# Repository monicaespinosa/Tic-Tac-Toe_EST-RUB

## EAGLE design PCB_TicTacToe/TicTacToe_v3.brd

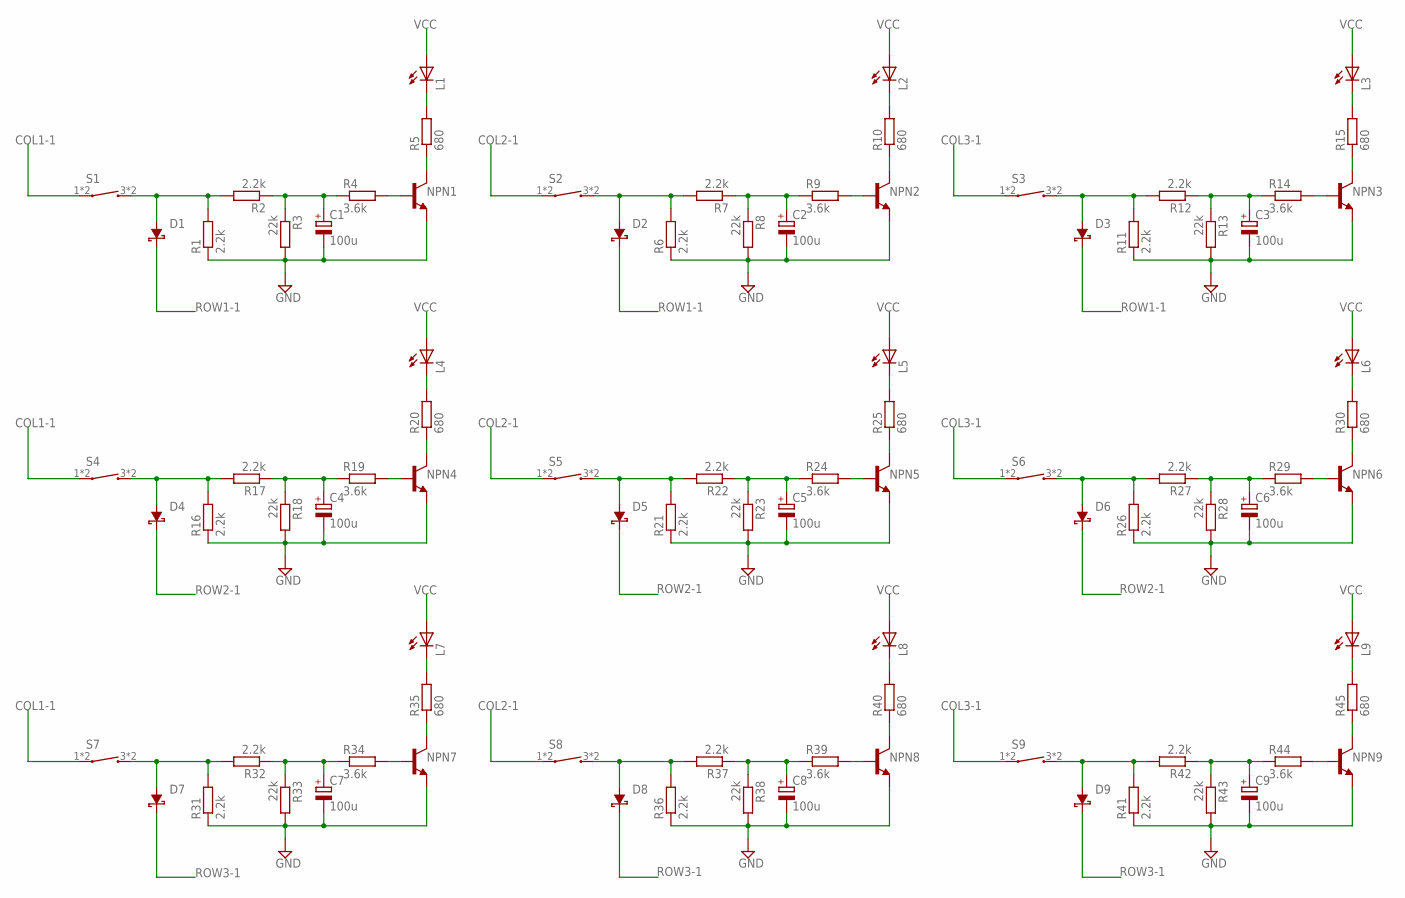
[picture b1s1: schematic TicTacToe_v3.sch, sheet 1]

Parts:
C1, C2, C3, C4, C5, C6, C7, C8, C9: 100u; T490A-COND
D1, D2, D3, D4, D5, D6, D7, D8, D9: PMEG3010EH; PMEG3010EH-SCHOTTKYDIODE
L1, L2, L3, L4, L5, L6, L7, L8, L9: 150060BS75003; WL-SMCW-LED(BLUE)
NPN1, NPN2, NPN3, NPN4, NPN5, NPN6, NPN7, NPN8, NPN9: BC848; BC848-NPN
R1, R2, R6, R7, R11, R12, R16, R17, R21, R22, R26, R27, R31, R32, R36, R37, R41, R42: 2.2k; R0603
R3, R8, R13, R18, R23, R28, R33, R38, R43: 22k; R0603
R4, R9, R14, R19, R24, R29, R34, R39, R44: 3.6k; R0603
R5, R10, R15, R20, R25, R30, R35, R40, R45: 680; R0603
S1, S2, S3, S4, S5, S6, S7, S8, S9: PTS647; PTS647-TACTSWITCH

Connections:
COL1-1: S1.1, S1.2 (1), S4.1, S4.2 (1), S7.1, S7.2 (1); also elsewhere on the board
COL2-1: S2.1, S2.2 (1), S5.1, S5.2 (1), S8.1, S8.2 (1); also elsewhere on the board
COL3-1: S3.1, S3.2 (1), S6.1, S6.2 (1), S9.1, S9.2 (1); also elsewhere on the board
GND: C1.2 (-), C2.2 (-), C3.2 (-), C4.2 (-), C5.2 (-), C6.2 (-), C7.2 (-), C8.2 (-), C9.2 (-), NPN1.2 (E), NPN2.2 (E), NPN3.2 (E), NPN4.2 (E), NPN5.2 (E), NPN6.2 (E), NPN7.2 (E), NPN8.2 (E), NPN9.2 (E), R1.1, R3.2, R6.1, R8.2, R11.1, R13.2, R16.1, R18.2, R21.1, R23.2, R26.1, R28.2, R31.1, R33.2, R36.1, R38.2, R41.1, R43.2; also elsewhere on the board
unnamed: D1.2 (A), R1.2, R2.2, S1.3 (2), S1.4 (2)
unnamed: C1.1 (+), R2.1, R3.1, R4.1
unnamed: NPN1.1 (B), R4.2
unnamed: D2.2 (A), R6.2, R7.2, S2.3 (2), S2.4 (2)
unnamed: C2.1 (+), R7.1, R8.1, R9.1
unnamed: NPN1.3 (C), R5.1
unnamed: L1.1 (C), R5.2
unnamed: NPN2.1 (B), R9.2
unnamed: D4.2 (A), R16.2, R17.2, S4.3 (2), S4.4 (2)
unnamed: NPN2.3 (C), R10.1
unnamed: L2.1 (C), R10.2
unnamed: C4.1 (+), R17.1, R18.1, R19.1
unnamed: D3.2 (A), R11.2, R12.2, S3.3 (2), S3.4 (2)
unnamed: C3.1 (+), R12.1, R13.1, R14.1
unnamed: NPN3.1 (B), R14.2
unnamed: NPN3.3 (C), R15.1
unnamed: L3.1 (C), R15.2
unnamed: NPN4.1 (B), R19.2
unnamed: NPN4.3 (C), R20.1
unnamed: L4.1 (C), R20.2
unnamed: D5.2 (A), R21.2, R22.2, S5.3 (2), S5.4 (2)
unnamed: C5.1 (+), R22.1, R23.1, R24.1
unnamed: NPN5.1 (B), R24.2
unnamed: NPN5.3 (C), R25.1
unnamed: L5.1 (C), R25.2
unnamed: D6.2 (A), R26.2, R27.2, S6.3 (2), S6.4 (2)
unnamed: C6.1 (+), R27.1, R28.1, R29.1
unnamed: NPN6.1 (B), R29.2
unnamed: NPN6.3 (C), R30.1
unnamed: L6.1 (C), R30.2
unnamed: D7.2 (A), R31.2, R32.2, S7.3 (2), S7.4 (2)
unnamed: C7.1 (+), R32.1, R33.1, R34.1
unnamed: NPN7.1 (B), R34.2
unnamed: NPN7.3 (C), R35.1
unnamed: L7.1 (C), R35.2
unnamed: D8.2 (A), R36.2, R37.2, S8.3 (2), S8.4 (2)
unnamed: C8.1 (+), R37.1, R38.1, R39.1
unnamed: NPN8.1 (B), R39.2
unnamed: NPN8.3 (C), R40.1
unnamed: L8.1 (C), R40.2
unnamed: D9.2 (A), R41.2, R42.2, S9.3 (2), S9.4 (2)
unnamed: C9.1 (+), R42.1, R43.1, R44.1
unnamed: NPN9.1 (B), R44.2
unnamed: NPN9.3 (C), R45.1
unnamed: L9.1 (C), R45.2
ROW1-1: D1.1 (C), D2.1 (C), D3.1 (C); also elsewhere on the board
ROW2-1: D4.1 (C), D5.1 (C), D6.1 (C); also elsewhere on the board
ROW3-1: D7.1 (C), D8.1 (C), D9.1 (C); also elsewhere on the board
VCC: L1.2 (A), L2.2 (A), L3.2 (A), L4.2 (A), L5.2 (A), L6.2 (A), L7.2 (A), L8.2 (A), L9.2 (A); also elsewhere on the board

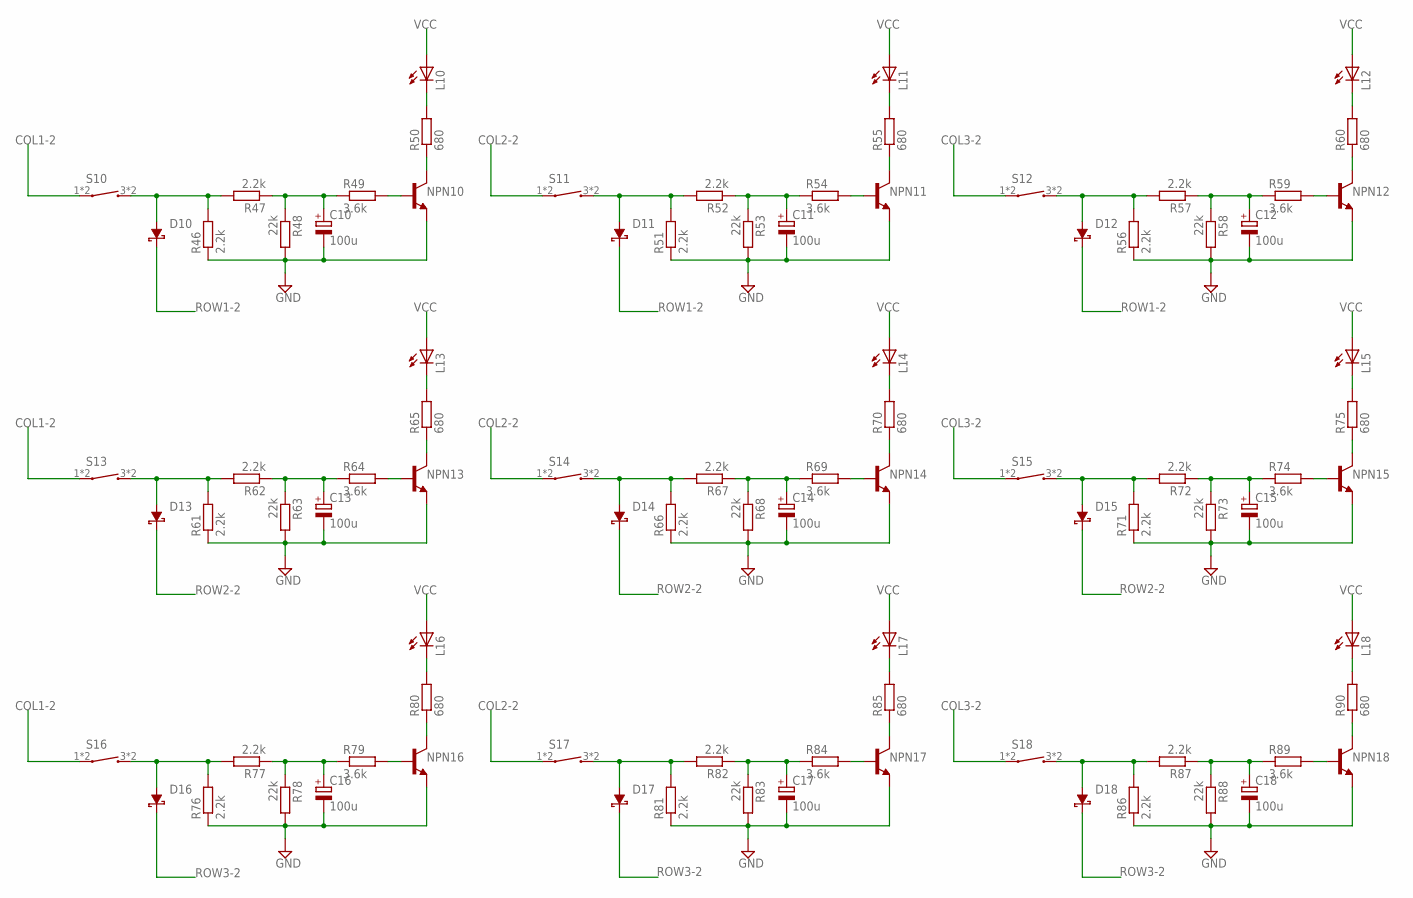
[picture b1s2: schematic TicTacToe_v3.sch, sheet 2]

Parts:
C10, C11, C12, C13, C14, C15, C16, C17, C18: 100u; T490A-COND
D10, D11, D12, D13, D14, D15, D16, D17, D18: PMEG3010EH; PMEG3010EH-SCHOTTKYDIODE
L10, L11, L12, L13, L14, L15, L16, L17, L18: 150060BS75003; WL-SMCW-LED(BLUE)
NPN10, NPN11, NPN12, NPN13, NPN14, NPN15, NPN16, NPN17, NPN18: BC848; BC848-NPN
R46, R47, R51, R52, R56, R57, R61, R62, R66, R67, R71, R72, R76, R77, R81, R82, R86, R87: 2.2k; R0603
R48, R53, R58, R63, R68, R73, R78, R83, R88: 22k; R0603
R49, R54, R59, R64, R69, R74, R79, R84, R89: 3.6k; R0603
R50, R55, R60, R65, R70, R75, R80, R85, R90: 680; R0603
S10, S11, S12, S13, S14, S15, S16, S17, S18: PTS647; PTS647-TACTSWITCH

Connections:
COL1-2: S10.1, S10.2 (1), S13.1, S13.2 (1), S16.1, S16.2 (1); also elsewhere on the board
COL2-2: S11.1, S11.2 (1), S14.1, S14.2 (1), S17.1, S17.2 (1); also elsewhere on the board
COL3-2: S12.1, S12.2 (1), S15.1, S15.2 (1), S18.1, S18.2 (1); also elsewhere on the board
GND: C10.2 (-), C11.2 (-), C12.2 (-), C13.2 (-), C14.2 (-), C15.2 (-), C16.2 (-), C17.2 (-), C18.2 (-), NPN10.2 (E), NPN11.2 (E), NPN12.2 (E), NPN13.2 (E), NPN14.2 (E), NPN15.2 (E), NPN16.2 (E), NPN17.2 (E), NPN18.2 (E), R46.1, R48.2, R51.1, R53.2, R56.1, R58.2, R61.1, R63.2, R66.1, R68.2, R71.1, R73.2, R76.1, R78.2, R81.1, R83.2, R86.1, R88.2; also elsewhere on the board
unnamed: D10.2 (A), R46.2, R47.2, S10.3 (2), S10.4 (2)
unnamed: C10.1 (+), R47.1, R48.1, R49.1
unnamed: NPN10.1 (B), R49.2
unnamed: NPN10.3 (C), R50.1
unnamed: L10.1 (C), R50.2
unnamed: D11.2 (A), R51.2, R52.2, S11.3 (2), S11.4 (2)
unnamed: C11.1 (+), R52.1, R53.1, R54.1
unnamed: NPN11.1 (B), R54.2
unnamed: NPN11.3 (C), R55.1
unnamed: L11.1 (C), R55.2
unnamed: D12.2 (A), R56.2, R57.2, S12.3 (2), S12.4 (2)
unnamed: C12.1 (+), R57.1, R58.1, R59.1
unnamed: NPN12.1 (B), R59.2
unnamed: NPN12.3 (C), R60.1
unnamed: L12.1 (C), R60.2
unnamed: D13.2 (A), R61.2, R62.2, S13.3 (2), S13.4 (2)
unnamed: C13.1 (+), R62.1, R63.1, R64.1
unnamed: NPN13.1 (B), R64.2
unnamed: NPN13.3 (C), R65.1
unnamed: L13.1 (C), R65.2
unnamed: D14.2 (A), R66.2, R67.2, S14.3 (2), S14.4 (2)
unnamed: C14.1 (+), R67.1, R68.1, R69.1
unnamed: NPN14.1 (B), R69.2
unnamed: NPN14.3 (C), R70.1
unnamed: L14.1 (C), R70.2
unnamed: D15.2 (A), R71.2, R72.2, S15.3 (2), S15.4 (2)
unnamed: C15.1 (+), R72.1, R73.1, R74.1
unnamed: NPN15.1 (B), R74.2
unnamed: NPN15.3 (C), R75.1
unnamed: L15.1 (C), R75.2
unnamed: D16.2 (A), R76.2, R77.2, S16.3 (2), S16.4 (2)
unnamed: C16.1 (+), R77.1, R78.1, R79.1
unnamed: NPN16.1 (B), R79.2
unnamed: NPN16.3 (C), R80.1
unnamed: L16.1 (C), R80.2
unnamed: D17.2 (A), R81.2, R82.2, S17.3 (2), S17.4 (2)
unnamed: C17.1 (+), R82.1, R83.1, R84.1
unnamed: NPN17.1 (B), R84.2
unnamed: NPN17.3 (C), R85.1
unnamed: L17.1 (C), R85.2
unnamed: D18.2 (A), R86.2, R87.2, S18.3 (2), S18.4 (2)
unnamed: C18.1 (+), R87.1, R88.1, R89.1
unnamed: NPN18.1 (B), R89.2
unnamed: NPN18.3 (C), R90.1
unnamed: L18.1 (C), R90.2
ROW1-2: D10.1 (C), D11.1 (C), D12.1 (C); also elsewhere on the board
ROW2-2: D13.1 (C), D14.1 (C), D15.1 (C); also elsewhere on the board
ROW3-2: D16.1 (C), D17.1 (C), D18.1 (C); also elsewhere on the board
VCC: L10.2 (A), L11.2 (A), L12.2 (A), L13.2 (A), L14.2 (A), L15.2 (A), L16.2 (A), L17.2 (A), L18.2 (A); also elsewhere on the board

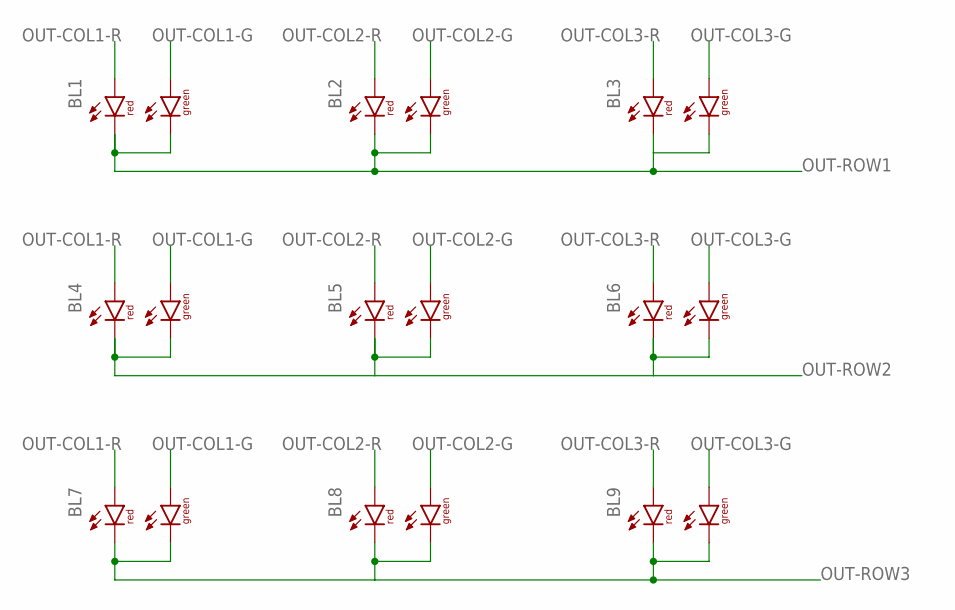
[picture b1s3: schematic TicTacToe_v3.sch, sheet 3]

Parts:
BL1, BL2, BL3, BL4, BL5, BL6, BL7, BL8, BL9: APHBM2012ETSGT(R/G); APHBM2012ETSGTC-BICOLORLED(R/G)

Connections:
OUT-COL1-G: BL1.4 (AG), BL4.4 (AG), BL7.4 (AG); also elsewhere on the board
OUT-COL1-R: BL1.1 (AR), BL4.1 (AR), BL7.1 (AR); also elsewhere on the board
OUT-COL2-G: BL2.4 (AG), BL5.4 (AG), BL8.4 (AG); also elsewhere on the board
OUT-COL2-R: BL2.1 (AR), BL5.1 (AR), BL8.1 (AR); also elsewhere on the board
OUT-COL3-G: BL3.4 (AG), BL6.4 (AG), BL9.4 (AG); also elsewhere on the board
OUT-COL3-R: BL3.1 (AR), BL6.1 (AR), BL9.1 (AR); also elsewhere on the board
OUT-ROW1: BL1.2 (CR), BL1.3 (CG), BL2.2 (CR), BL2.3 (CG), BL3.2 (CR), BL3.3 (CG); also elsewhere on the board
OUT-ROW2: BL4.2 (CR), BL4.3 (CG), BL5.2 (CR), BL5.3 (CG), BL6.2 (CR), BL6.3 (CG); also elsewhere on the board
OUT-ROW3: BL7.2 (CR), BL7.3 (CG), BL8.2 (CR), BL8.3 (CG), BL9.2 (CR), BL9.3 (CG); also elsewhere on the board

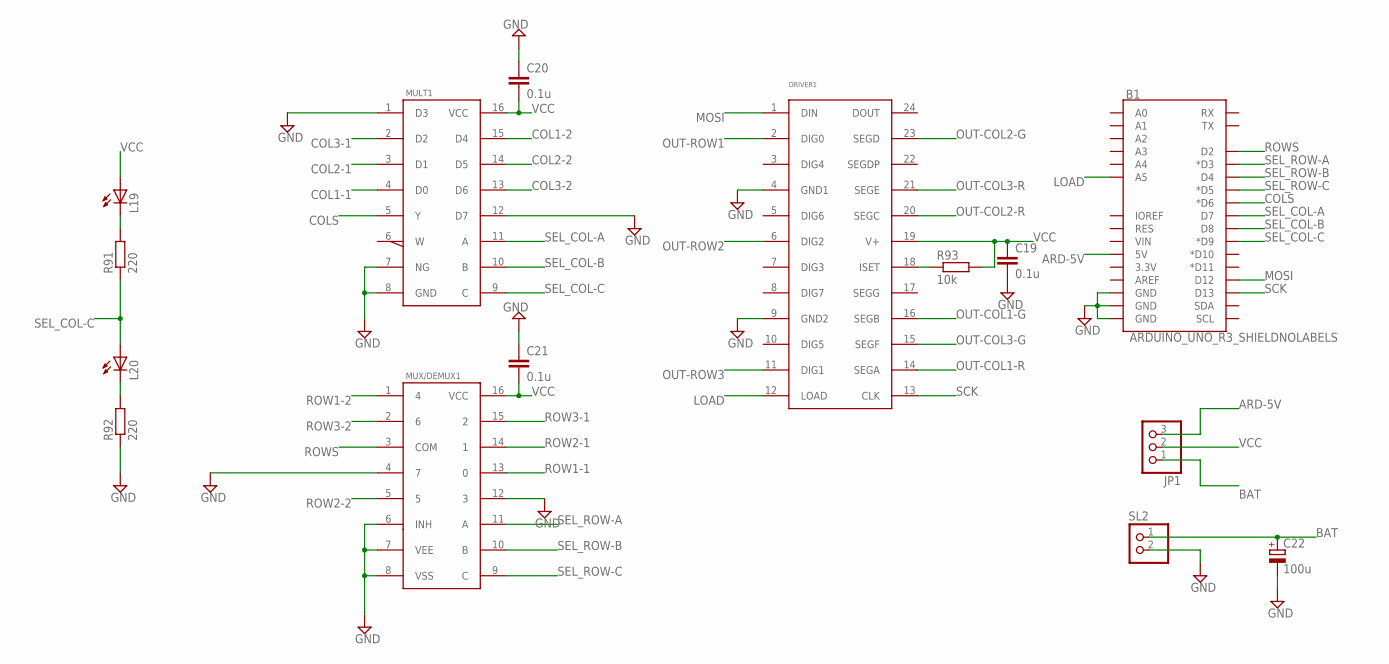
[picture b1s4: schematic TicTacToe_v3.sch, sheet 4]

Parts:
B1: ARDUINO_UNO_R3_SHIELDNOLABELS; UNO_R3_SHIELD_NOLABELS
C19, C20, C21: 0.1u; C0603
C22: 100u; T490A-COND
DRIVER1: MAX7219; MAX7219EWGT
JP1: PINHD-1X3; 1X03
L19, L20: 150060BS75003; WL-SMCW-LED(BLUE)
MULT1: SN74F151BDR; SOIC16N
MUX/DEMUX1: TC4051B; SOIC16N
R91, R92: 220; R0603
R93: 10k; R0603
SL2: PINHD-1X2; 1X02

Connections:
ARD-5V: B1.5V, JP1.3
BAT: C22.1 (+), JP1.1, SL2.1
COL1-1: MULT1.4 (D0); also elsewhere on the board
COL1-2: MULT1.15 (D4); also elsewhere on the board
COL2-1: MULT1.3 (D1); also elsewhere on the board
COL2-2: MULT1.14 (D5); also elsewhere on the board
COL3-1: MULT1.2 (D2); also elsewhere on the board
COL3-2: MULT1.13 (D6); also elsewhere on the board
COLS: B1.D6 (*D6), MULT1.5 (Y)
GND: B1.GND@0 (GND), B1.GND@1 (GND), B1.GND@2 (GND), C19.2, C20.1, C21.1, C22.2 (-), DRIVER1.4 (GND1), DRIVER1.9 (GND2), MULT1.1 (D3), MULT1.7 (NG), MULT1.8 (GND), MULT1.12 (D7), MUX/DEMUX1.4 (7), MUX/DEMUX1.6 (INH), MUX/DEMUX1.7 (VEE), MUX/DEMUX1.8 (VSS), MUX/DEMUX1.12 (3), R92.1, SL2.2; also elsewhere on the board
LOAD: B1.A5, DRIVER1.12 (LOAD)
MOSI: B1.D12, DRIVER1.1 (DIN)
unnamed: DRIVER1.18 (ISET), R93.1
unnamed: L19.1 (C), R91.2
unnamed: L20.1 (C), R92.2
OUT-COL1-G: DRIVER1.16 (SEGB); also elsewhere on the board
OUT-COL1-R: DRIVER1.14 (SEGA); also elsewhere on the board
OUT-COL2-G: DRIVER1.23 (SEGD); also elsewhere on the board
OUT-COL2-R: DRIVER1.20 (SEGC); also elsewhere on the board
OUT-COL3-G: DRIVER1.15 (SEGF); also elsewhere on the board
OUT-COL3-R: DRIVER1.21 (SEGE); also elsewhere on the board
OUT-ROW1: DRIVER1.2 (DIG0); also elsewhere on the board
OUT-ROW2: DRIVER1.6 (DIG2); also elsewhere on the board
OUT-ROW3: DRIVER1.11 (DIG1); also elsewhere on the board
ROW1-1: MUX/DEMUX1.13 (0); also elsewhere on the board
ROW1-2: MUX/DEMUX1.1 (4); also elsewhere on the board
ROW2-1: MUX/DEMUX1.14 (1); also elsewhere on the board
ROW2-2: MUX/DEMUX1.5; also elsewhere on the board
ROW3-1: MUX/DEMUX1.15 (2); also elsewhere on the board
ROW3-2: MUX/DEMUX1.2 (6); also elsewhere on the board
ROWS: B1.D2, MUX/DEMUX1.3 (COM)
SCK: B1.D13, DRIVER1.13 (CLK)
SEL_COL-A: B1.D7, MULT1.11 (A)
SEL_COL-B: B1.D8, MULT1.10 (B)
SEL_COL-C: B1.D9 (*D9), L20.2 (A), MULT1.9 (C), R91.1
SEL_ROW-A: B1.D3 (*D3), MUX/DEMUX1.11 (A)
SEL_ROW-B: B1.D4, MUX/DEMUX1.10 (B)
SEL_ROW-C: B1.D5 (*D5), MUX/DEMUX1.9 (C)
VCC: C19.1, C20.2, C21.2, DRIVER1.19 (V+), JP1.2, L19.2 (A), MULT1.16 (VCC), MUX/DEMUX1.16 (VCC), R93.2; also elsewhere on the board

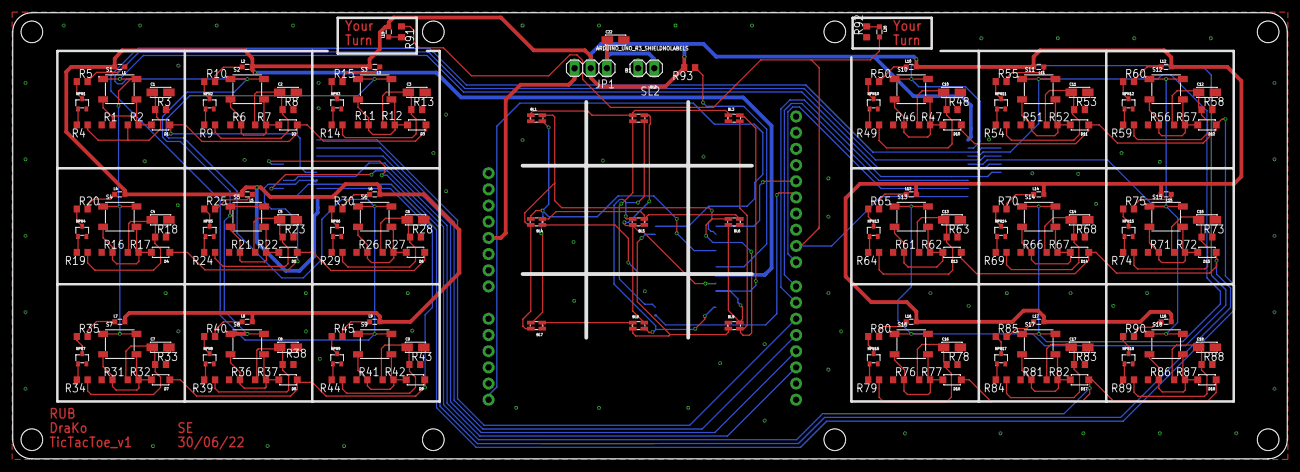
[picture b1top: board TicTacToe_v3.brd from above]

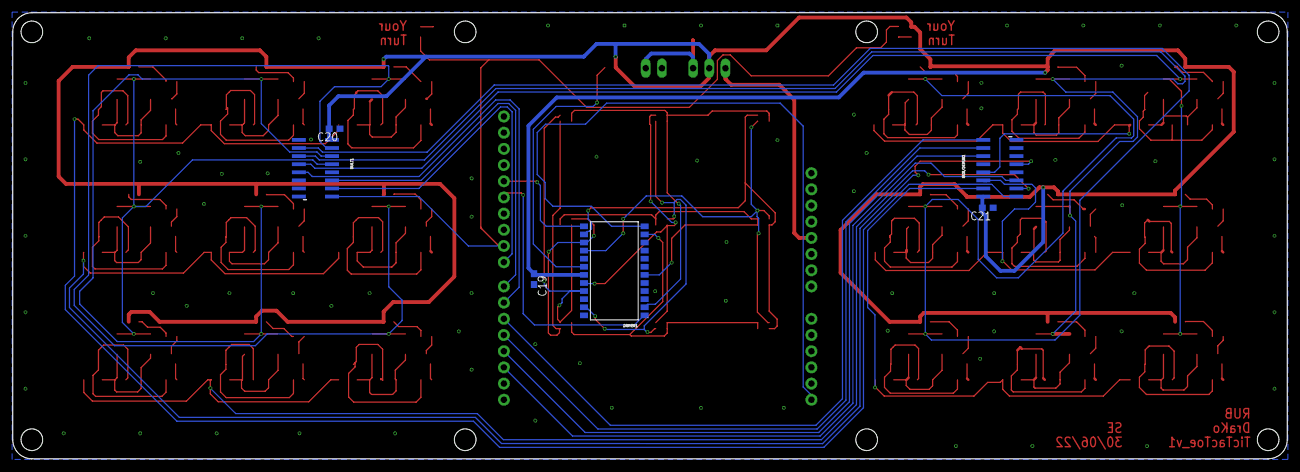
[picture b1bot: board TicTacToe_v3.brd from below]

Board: 2 copper layers, 200.0 x 70.0 mm, 204 parts (6 on the bottom side), 129 nets.

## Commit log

2022-08-18 Add files via upload
    Basically, the program works as a multilayer Tic Tac Toe ran from an Arduino R3.
    Surely in future changes it will be added a single player mode against a Minimax
    algorithm - my idea is to program that as an Arduino library in C++, in that way
    the Arduino code only manages inputs, outputs and Hardware configuration.
2023-11-20 PCB - finished Prototype - Tic-Tac-Toe functions
    This board also needs the Sparkfun boards - Library for the Arduino Uno footprint.
2023-11-20 Create README.md - PCB
    Here goes the description and visualization of the PCB in Eagle and all relevant information

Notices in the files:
parts and their libraries:
SparkFun-Boards: Licensing: Creative Commons ShareAlike 4.0 International - https://creativecommons.org/licenses/by-sa/4.0
